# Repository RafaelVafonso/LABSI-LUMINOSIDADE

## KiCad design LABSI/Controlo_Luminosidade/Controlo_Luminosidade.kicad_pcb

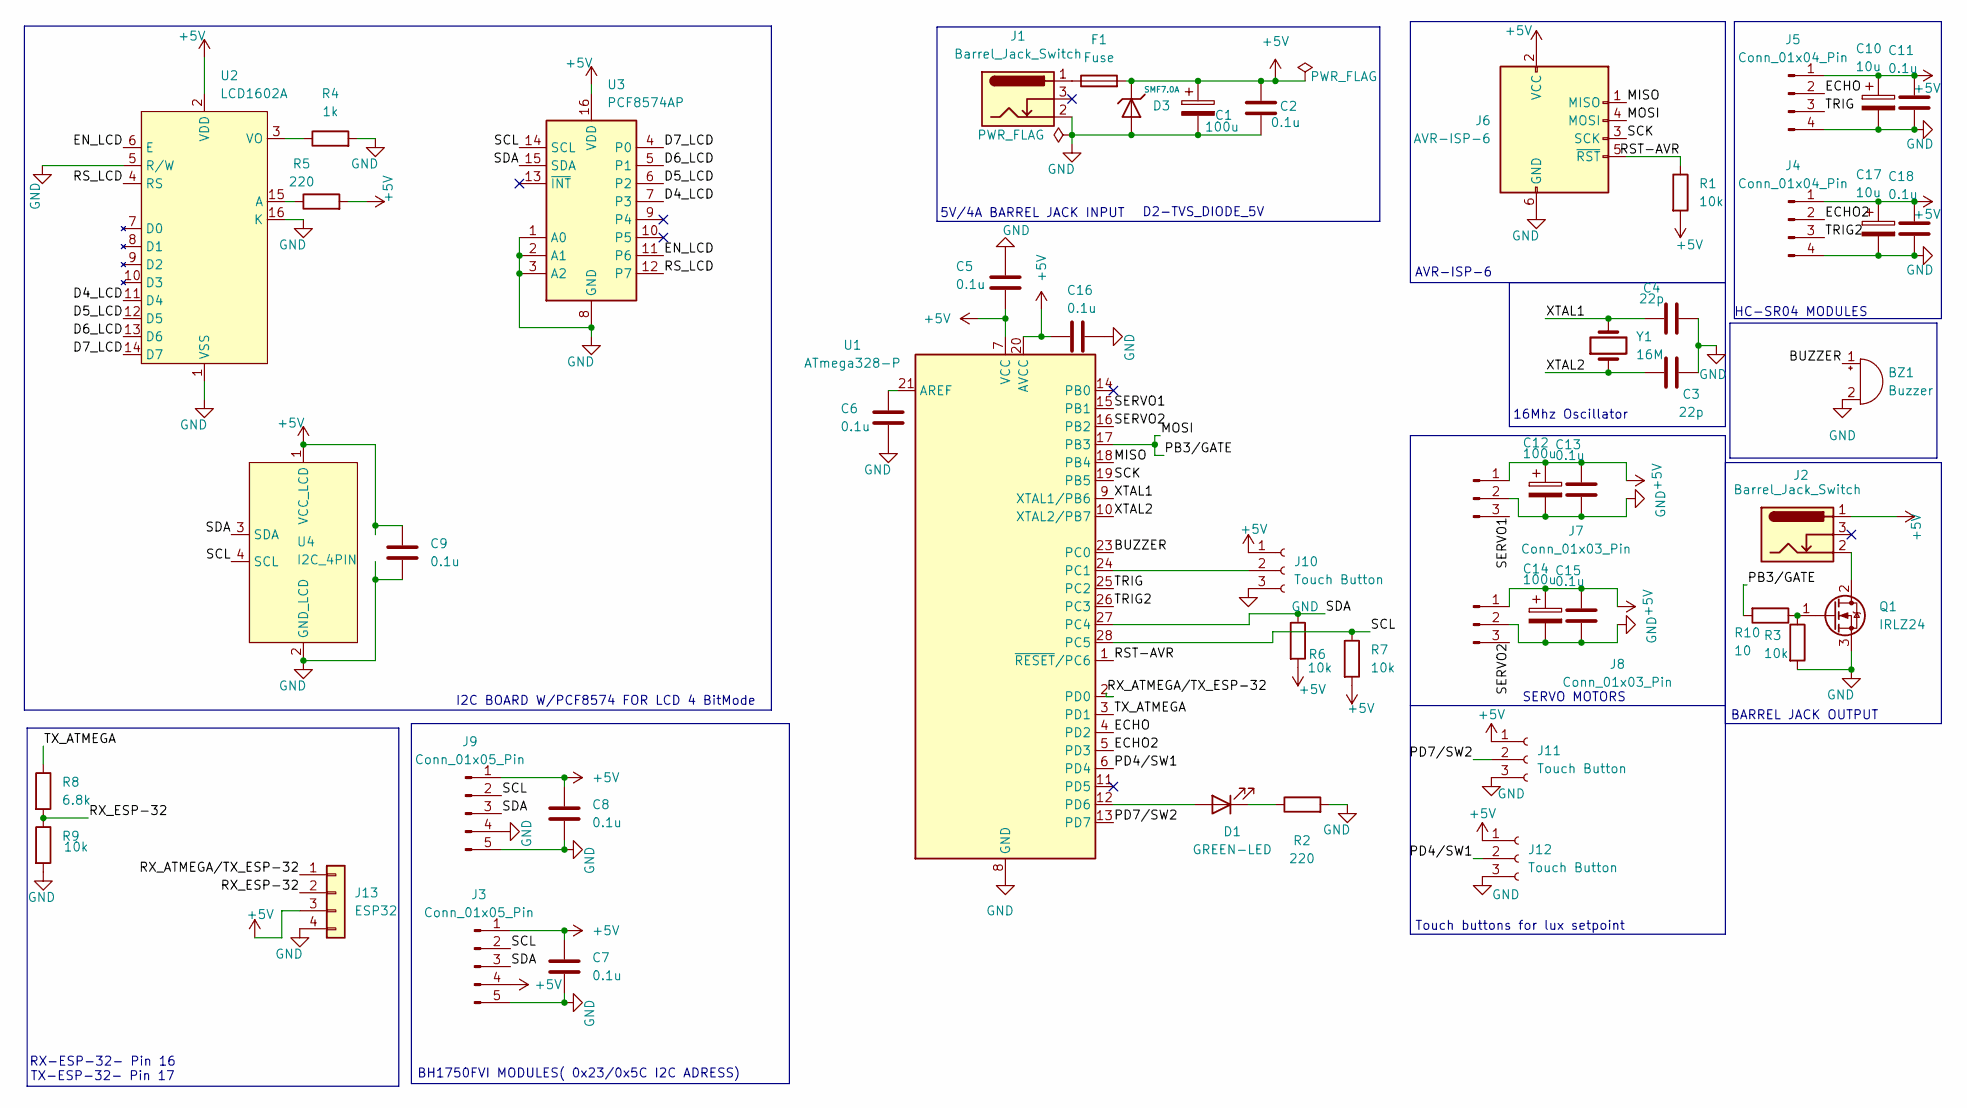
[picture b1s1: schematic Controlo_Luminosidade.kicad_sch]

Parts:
BZ1: Buzzer; Buzzer_12x9.5RM7.6
C1, C12, C14: 100u; C_Radial_D6.3mm_H11.0mm_P2.50mm
C2, C5, C6, C7, C8, C11, C13, C15, C16, C18: 0.1u; C_Disc_D3.0mm_W2.0mm_P2.50mm
C3, C4: 22p; C_Disc_D3.0mm_W2.0mm_P2.50mm
C9: 0.1u
C10, C17: 10u; C_Radial_D6.3mm_H11.0mm_P2.50mm
D1: GREEN-LED; LED_D5.0mm
D3: SMF7.0A; D_SMA; Breakdown Voltage 8.6V; Part SMF7.0A; LCSC C41376088
F1: Fuse; FUSAD2722W65L2250D600
J1, J2: Barrel_Jack_Switch; BarrelJack_Horizontal
J3, J9: Conn_01x05_Pin; PinHeader_1x05_P2.54mm_Vertical
J4, J5: Conn_01x04_Pin; PinSocket_1x04_P2.54mm_Vertical
J6: AVR-ISP-6; PinHeader_2x03_P2.54mm_Vertical
J7, J8: Conn_01x03_Pin; PinHeader_1x03_P2.54mm_Vertical
J10, J11, J12: Touch Button; PinSocket_1x03_P2.54mm_Vertical
J13: ESP32; PinSocket_1x04_P2.54mm_Vertical
Q1: IRLZ24; TO-220-3_Vertical
R1, R3, R6, R7, R9: 10k; R_Axial_DIN0204_L3.6mm_D1.6mm_P5.08mm_Horizontal
R2: 220; R_Axial_DIN0204_L3.6mm_D1.6mm_P5.08mm_Horizontal
R4: 1k
R5: 220
R8: 6.8k; R_Axial_DIN0204_L3.6mm_D1.6mm_P5.08mm_Horizontal
R10: 10; R_Axial_DIN0204_L3.6mm_D1.6mm_P5.08mm_Horizontal
U1: ATmega328-P; DIP-28_W7.62mm
U2: LCD1602A
U3: PCF8574AP
U4: I2C_4PIN; PinSocket_2x02_P2.54mm_Vertical
Y1: 16M; Crystal_HC49-4H_Vertical

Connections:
+5V: C1.1, C2.1, C5.1, C7.1, C8.1, C9.1, C10.1, C11.1, C12.1, C13.1, C14.1, C15.1, C16.1, C17.1, C18.1, D3.1, F1.2, J2.1, J3.1, J3.4, J4.1, J5.1, J6.2 (VCC), J7.1, J8.1, J9.1, J10.1, J11.1, J12.1, J13.3, R1.2, R5.2, R6.2, R7.2, U1.7 (VCC), U1.20 (AVCC), U2.2 (VDD), U3.16 (VDD), U4.1 (VCC_LCD)
/BUZZER: BZ1.1 (+), U1.23 (PC0)
/ECHO: J5.2, U1.4 (PD2)
/ECHO2: J4.2, U1.5 (PD3)
/MISO: J6.1 (MISO), U1.18 (PB4)
/MOSI: J6.4 (MOSI), R10.2, U1.17 (PB3)
/PD4/SW1: J12.2, U1.6 (PD4)
/PD7/SW2: J11.2, U1.13 (PD7)
/RST-AVR: J6.5 (~RST), R1.1, U1.1 (~RESET/PC6)
/RX_ATMEGA/TX_ESP-32: J13.1, U1.2 (PD0)
/RX_ESP-32: J13.2, R8.2, R9.1
/SCK: J6.3 (SCK), U1.19 (PB5)
/SCL: J3.2, J9.2, R7.1, U1.28 (PC5), U3.14 (SCL), U4.4 (SCL)
/SDA: J3.3, J9.3, R6.1, U1.27 (PC4), U3.15 (SDA), U4.3 (SDA)
/SERVO1: J7.3, U1.15 (PB1)
/SERVO2: J8.3, U1.16 (PB2)
/TRIG: J5.3, U1.25 (PC2)
/TRIG2: J4.3, U1.26 (PC3)
/TX_ATMEGA: R8.1, U1.3 (PD1)
/XTAL1: C4.1, U1.9 (XTAL1/PB6), Y1.2
/XTAL2: C3.1, U1.10 (XTAL2/PB7), Y1.1
GND: BZ1.2 (-), C1.2, C2.2, C3.2, C4.2, C5.2, C6.2, C7.2, C8.2, C9.2, C10.2, C11.2, C12.2, C13.2, C14.2, C15.2, C16.2, C17.2, C18.2, D3.2, J1.2, J3.5, J4.4, J5.4, J6.6 (GND), J7.2, J8.2, J9.4, J9.5, J10.3, J11.3, J12.3, J13.4, Q1.3 (S), R2.2, R3.2, R4.2, R9.2, U1.8 (GND), U1.22 (GND), U2.1 (VSS), U2.5 (R/W), U2.16 (K), U3.1 (A0), U3.2 (A1), U3.3 (A2), U3.8 (GND), U4.2 (GND_LCD)
unnamed: D1.2 (A), U1.12 (PD6)
unnamed: D1.1 (K), R2.1
unnamed: F1.1, J1.1
unnamed: J10.2, U1.24 (PC1)
unnamed: J2.2, Q1.2 (D)
unnamed: Q1.1 (G), R3.1, R10.1
unnamed: R4.1, U2.3 (VO)
unnamed: R5.1, U2.15 (A)
unnamed: C6.1, U1.21 (AREF)
unnamed: U2.4 (RS), U3.12 (P7)
unnamed: U2.6 (E), U3.11 (P6)
unnamed: U2.11 (D4), U3.7 (P3)
unnamed: U2.12 (D5), U3.6 (P2)
unnamed: U2.13 (D6), U3.5 (P1)
unnamed: U2.14 (D7), U3.4 (P0)

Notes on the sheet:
D2-TVS_DIODE_5V
RX-ESP-32- Pin 16 TX-ESP-32- Pin 17
I2C BOARD W/PCF8574 FOR LCD 4 BitMode
Touch buttons for lux setpoint
16Mhz Oscillator
5V/4A BARREL JACK INPUT
SERVO MOTORS
BH1750FVI MODULES( 0x23/0x5C I2C ADRESS)
AVR-ISP-6
BARREL JACK OUTPUT
HC-SR04 MODULES

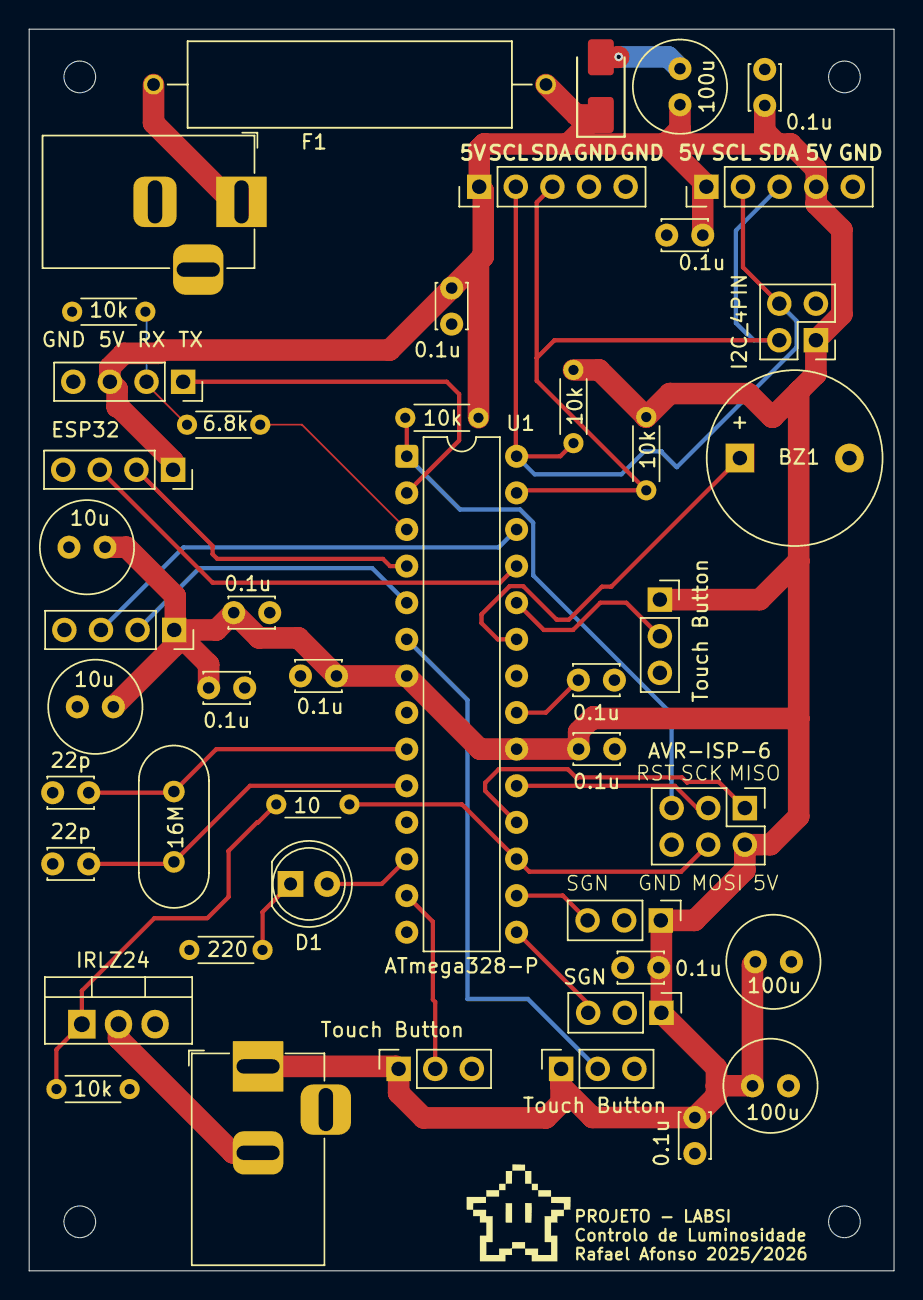
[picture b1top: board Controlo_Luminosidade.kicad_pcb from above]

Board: 2 copper layers, 60.0 x 86.1 mm, 46 parts (0 on the bottom side), 29 nets.

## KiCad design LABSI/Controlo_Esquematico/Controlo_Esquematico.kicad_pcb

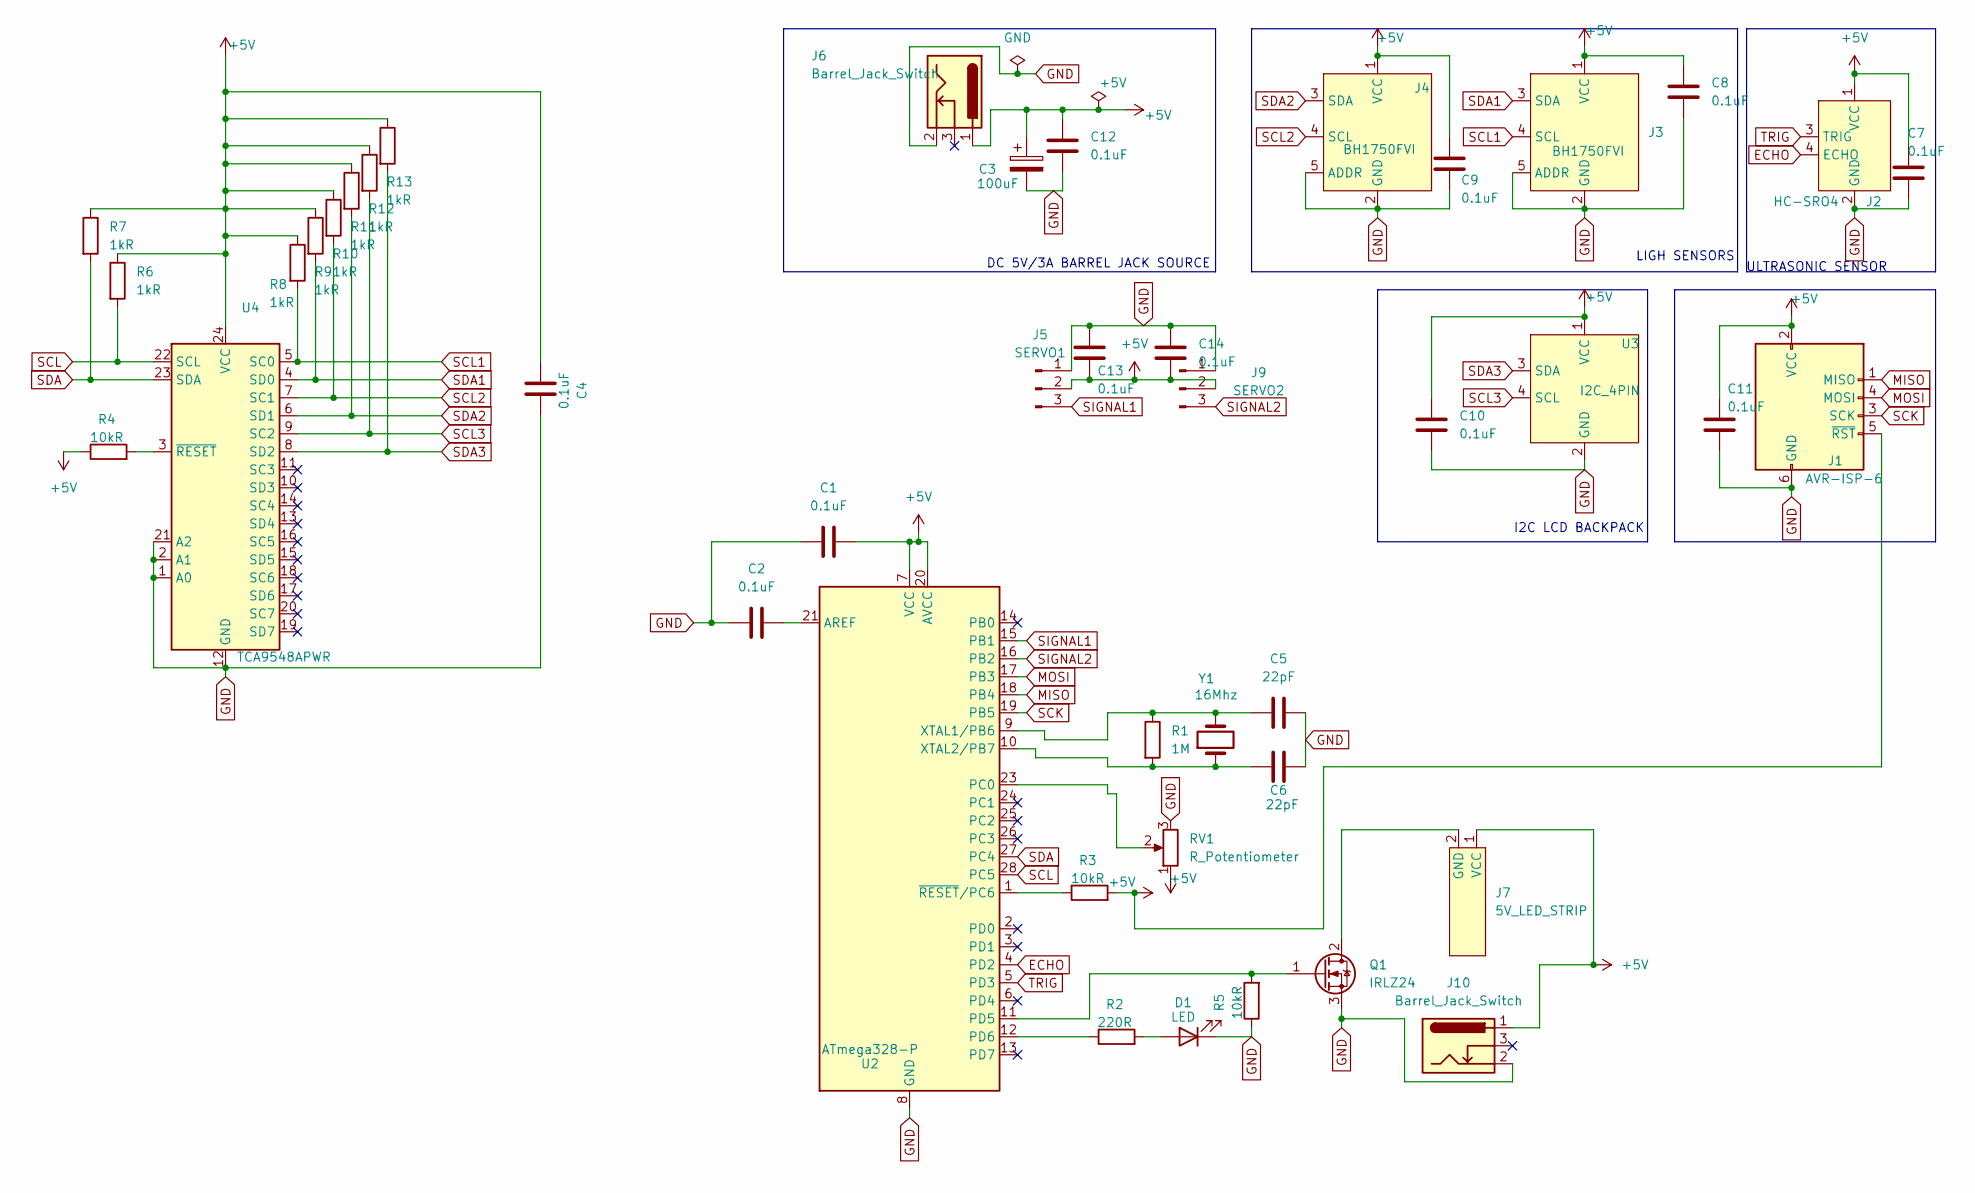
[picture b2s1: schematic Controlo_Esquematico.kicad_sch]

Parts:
C1, C2, C4, C7, C8, C9, C10, C11, C12, C13, C14: 0.1uF; C_Disc_D3.0mm_W2.0mm_P2.50mm
C3: 100uF; CP_Radial_D4.0mm_P1.50mm
C5, C6: 22pF; C_Disc_D3.0mm_W2.0mm_P2.50mm
D1: LED; LED_D5.0mm
J1: AVR-ISP-6; PinHeader_2x03_P2.54mm_Vertical
J2: HC-SRO4; PinHeader_1x04_P2.54mm_Vertical
J3, J4: BH1750FVI; PinHeader_1x05_P2.54mm_Vertical
J5: SERVO1; PinHeader_1x03_P2.54mm_Vertical
J6, J10: Barrel_Jack_Switch; CUI_PJ-067B
J7: 5V_LED_STRIP
J9: SERVO2; PinHeader_1x03_P2.54mm_Vertical
Q1: IRLZ24; TO-220-3_Vertical
R1: 1M; R_Axial_DIN0204_L3.6mm_D1.6mm_P5.08mm_Horizontal
R2: 220R; R_Axial_DIN0204_L3.6mm_D1.6mm_P5.08mm_Horizontal
R3, R4, R5: 10kR; R_Axial_DIN0204_L3.6mm_D1.6mm_P5.08mm_Horizontal
R6, R7, R8, R9, R10, R11, R12, R13: 1kR; R_Axial_DIN0204_L3.6mm_D1.6mm_P5.08mm_Horizontal
RV1: R_Potentiometer; Potentiometer_Alps_RK163_Single_Horizontal
U2: ATmega328-P; DIP-28_W7.62mm
U3: I2C_4PIN; PinHeader_2x02_P2.54mm_Vertical
U4: TCA9548APWR; MODULE_2717
Y1: 16Mhz; Crystal_HC49-4H_Vertical

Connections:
+5V: C1.2, C3.1, C4.1, C7.1, C8.1, C9.1, C10.1, C11.1, C12.1, C13.1, C14.1, J1.2 (VCC), J1.5 (~RST), J2.1 (VCC), J3.1 (VCC), J4.1 (VCC), J5.2, J6.1, J7.1 (VCC), J9.2, J10.1, R3.2, R4.1, R6.1, R7.1, R8.1, R9.1, R10.1, R11.1, R12.1, R13.1, RV1.1, U2.7 (VCC), U2.20 (AVCC), U3.1 (VCC), U4.24 (VCC)
ECHO: J2.4 (ECHO), U2.4 (PD2)
GND: C1.1, C2.1, C3.2, C4.2, C5.2, C6.2, C7.2, C8.2, C9.2, C10.2, C11.2, C12.2, C13.2, C14.2, D1.1 (K), J1.6 (GND), J2.2 (GND), J3.2 (GND), J3.5 (ADDR), J4.2 (GND), J4.5 (ADDR), J5.1, J6.2, J9.1, J10.2, Q1.3 (S), R5.1, RV1.3, U2.8 (GND), U2.22 (GND), U3.2 (GND), U4.1 (A0), U4.2 (A1), U4.12 (GND), U4.21 (A2)
MISO: J1.1 (MISO), U2.18 (PB4)
MOSI: J1.4 (MOSI), U2.17 (PB3)
unnamed: D1.2 (A), R2.2
unnamed: J7.2 (GND), Q1.2 (D)
unnamed: Q1.1 (G), R5.2, U2.11 (PD5)
unnamed: C2.2, U2.21 (AREF)
unnamed: RV1.2, U2.23 (PC0)
unnamed: R2.1, U2.12 (PD6)
unnamed: C5.1, R1.1, U2.9 (XTAL1/PB6), Y1.2
unnamed: C6.1, R1.2, U2.10 (XTAL2/PB7), Y1.1
unnamed: R3.1, U2.1 (~RESET/PC6)
unnamed: R4.2, U4.3 (~RESET)
SCK: J1.3 (SCK), U2.19 (PB5)
SCL: R6.2, U2.28 (PC5), U4.22 (SCL)
SCL1: J3.4 (SCL), R8.2, U4.5 (SC0)
SCL2: J4.4 (SCL), R10.2, U4.7 (SC1)
SCL3: R12.2, U3.4 (SCL), U4.9 (SC2)
SDA: R7.2, U2.27 (PC4), U4.23 (SDA)
SDA1: J3.3 (SDA), R9.2, U4.4 (SD0)
SDA2: J4.3 (SDA), R11.2, U4.6 (SD1)
SDA3: R13.2, U3.3 (SDA), U4.8 (SD2)
SIGNAL1: J5.3, U2.15 (PB1)
SIGNAL2: J9.3, U2.16 (PB2)
TRIG: J2.3 (TRIG), U2.5 (PD3)

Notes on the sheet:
LIGH SENSORS
ULTRASONIC SENSOR
I2C LCD BACKPACK
DC 5V/3A BARREL JACK SOURCE

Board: 2 copper layers, 42 parts (0 on the bottom side), 26 nets, no tracks yet.

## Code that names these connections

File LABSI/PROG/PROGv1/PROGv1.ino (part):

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
#define MODE_AUTOMATIC 0
#define MODE_MANUAL 1
#define BOTAO_TOUCH PC1
#define BOTAO_MAIS PD4 // Botão Aumentar
#define BOTAO_MENOS PD7 // Botão Diminuir
#define BUZZER_PIN PC0 // Buzzer (PC0)

// --- CONFIGURAÇÃO UART (ESP32) ---
#define BAUD 9600
#define UBRR_VAL ((F_CPU/16/BAUD)-1)

#define SONAR1_TRIG PC2
#define SONAR1_ECHO PD2
#define SONAR2_TRIG PC3
#define SONAR2_ECHO PD3
// 20 cm ~ 1156 us de echo -> com Timer1 a 4 us/tick => ~290 ticks
#define SONAR_THRESHOLD_TICKS_20CM 290
#define LUX_STEP 50
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#define EEP_POS1_ADDR (uint16_t*)0x00
#define EEP_POS2_ADDR (uint16_t*)0x02

#define GATE_PIN PB3
#define MAX_LED_PWM 255
// --- VARIÁVEIS DE CONTROLO DE TEMPO E ESTADO ---
volatile uint16_t g_delay_counter_2ms = 0; // Contador principal, decrementa a cada 2ms
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	// Controlo do Buzzer
	if(g_buzzer_counter > 0) {
		g_buzzer_counter--;
		// Alterna o Buzzer (PC0) a cada 50ms (25 ticks)
		if(g_buzzer_counter % 25 == 0) {
			PORTC ^= (1 << BUZZER_PIN);
		}
	} else {
		PORTC &= ~(1 << BUZZER_PIN); // Desliga o Buzzer
	}
	g_contador++;
	if(g_contador >= 250) {
		PORTD ^= (1 << PD6);
		g_contador = 0;
	}
	g_display_counter++;

}
ISR(PCINT1_vect) {
	uint8_t current_state = PINC & (1 << PC1);
	if(current_state > g_prev_pc1_state) {
		// Transição de 0 para 1 detectada
		if(!g_mode_locked) {
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	TWCR |= (1 << TWEN);
	TWSR = 0;
	TWBR = 12;
	DDRC &= ~((1 << PC4) | (1 << PC5));
	PORTC |= (1 << PC4) | (1 << PC5);
}
void i2c_start(void) {
	TWCR = (1 << TWINT) | (1 << TWSTA) | (1 << TWEN);
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}
// --- Timer 0 for 2ms interrupt ---
void onda1Hz_init(void) {
	DDRD |= (1 << PD6);
	PORTD &= ~(1 << PD6);
	TCCR0A = (1 << WGM01); // CTC Mode
	TCCR0B = (1 << CS02) | (1 << CS00); // Prescaler 1024
	OCR0A = 31; // (16M / 1024) / (31+1) = 500 Hz (2ms)
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	OCR2A = 0;
}
void pwm_Servo_init(void) {
	DDRB |= (1 << PB1) | (1 << PB2);
	TCCR1A |= (1 << COM1A1) | (1 << COM1B1)| (1 << WGM11);//PC
	TCCR1B |= (1 << WGM13) | (1 << CS11) | (1 << CS10) | (1 << ICNC1); // prescaler 64, noise cancelling
	ICR1 = 2500; // 20 ms (50 Hz)
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	OCR1B = 188;
}
void buttons_inic(void) {
	// Botão touch PC1
	DDRC &= ~(1 << BOTAO_TOUCH);
	PORTC &= ~(1 << BOTAO_TOUCH);
	// Botões +/- em PD4 e PD7
	DDRD &= ~((1 << BOTAO_MAIS) | (1 << BOTAO_MENOS));
	PORTD &= ~((1 << BOTAO_MAIS) | (1 << BOTAO_MENOS));
	// BUZZER
	DDRC |= (1 << BUZZER_PIN);
	PORTC &= ~(1 << BUZZER_PIN);
	// Sonares: TRIG como saída, ECHO como entrada
	DDRC |= (1 << SONAR1_TRIG) | (1 << SONAR2_TRIG);
	DDRD &= ~((1 << SONAR1_ECHO) | (1 << SONAR2_ECHO));
	PORTD &= ~((1 << SONAR1_ECHO) | (1 << SONAR2_ECHO)); // sem pull-up
	// Interrupção de PC1 (botão touch)
	PCICR |= (1 << PCIE1);
	PCMSK1 |= (1 << PCINT9);
}
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  static uint8_t stable_state_1 = 0;
  static uint8_t stable_state_2 = 0;

  uint8_t trig_pin, echo_pin;
  uint32_t *last_time;
  uint8_t *stable_state;

  // Seleciona sonar
  if (sonar_id == 1) {
      trig_pin = SONAR1_TRIG;
      echo_pin = SONAR1_ECHO;
      last_time = &last_trigger_time_1;
      stable_state = &stable_state_1;
  } else {
      trig_pin = SONAR2_TRIG;
      echo_pin = SONAR2_ECHO;
      last_time = &last_trigger_time_2;
      stable_state = &stable_state_2;
  }
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  for (uint8_t i = 0; i < 3; i++)
  {
      // Trigger de 10 us
      PORTC &= ~(1 << trig_pin);
      delay_us(2);
      PORTC |= (1 << trig_pin);
      delay_us(10);
      PORTC &= ~(1 << trig_pin);

      delay_us(200); // evita eco imediato

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      uint16_t timeout = 0;

      // Espera echo subir
      while (!(PIND & (1 << echo_pin)) && timeout < 7500) timeout++;
      if (timeout >= 7500) { sei(); continue; }

      uint16_t start = TCNT1;
      timeout = 0;

      // Espera echo descer
      while ((PIND & (1 << echo_pin)) && timeout < 30000) timeout++;
      uint16_t end = TCNT1;

      sei();
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
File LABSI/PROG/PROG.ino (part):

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#define F_CPU 16000000UL    

// LCD PIN MAPPINGS (4-bit mode)
#define LCD_RS PORTD |= (1 << PD7)  // RS Pin 7
#define LCD_RS_LOW PORTD &= ~(1 << PD7)

#define LCD_EN PORTB |= (1 << PB0)  // EN Pin 8
#define LCD_EN_LOW PORTB &= ~(1 << PB0)

#define LCD_D4 PORTD |= (1 << PD0)  // D4 Pin 0
#define LCD_D4_LOW PORTD &= ~(1 << PD0)

#define LCD_D5 PORTD |= (1 << PD1)  // D5 Pin 1
#define LCD_D5_LOW PORTD &= ~(1 << PD1)

#define LCD_D6 PORTD |= (1 << PD4)  // D6 Pin 4
#define LCD_D6_LOW PORTD &= ~(1 << PD4)

#define LCD_D7 PORTD |= (1 << PD5)  // D7 Pin 5
#define LCD_D7_LOW PORTD &= ~(1 << PD5)


#define BH1750_ADDR1 0x23  //Default I2C address (0x23) ADDR GND
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    flag_2ms = 1;
    contador++;
    if (contador >= 250) { // 250 * 2ms = 0.5s
        PORTD ^= (1 << PD6); // Toggle PD6 for 1Hz signal check
        contador = 0;   
    }
    display_counter++;
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void lcd_init(void) {
    // Setup LCD control and data pins as outputs
    DDRB |= (1 << PB0);  // EN output
    DDRD |= (1 << PD0) | (1 << PD1) | (1 << PD4) | (1 << PD5) | (1 << PD7);  // D4-D7 and RS outputs
    
    delay_ms(50);  // Power-on wait
    
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    TWCR |= (1<< TWEN); //twi controla os pinos scl e sda
    TWSR = 0;// prescaler a 1
    TWBR =17;// SCL a 320khz
    DDRC &= ~((1 << PC4) | (1 << PC5)); 
    PORTC |= (1 << PC4) | (1 << PC5);
}

void i2c_start(void){
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}
void pwm_Servo_init(void){

DDRB |= (1 << PB1);
TCCR1A |= (1 << COM1A1) | (1 << WGM11);
TCCR1B |= (1 << WGM13) | (1 << CS11) | (1 << CS10);
ICR1 = 2500;
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}


// --- Timer 0 for 2ms interrupt (for timing and toggling PD6) ---
void onda1Hz_init(void) {
    DDRD |= (1 << PD6); // PD6 as output (LED check)
    PORTD &= ~(1 << PD6); // Initial state low

    // Timer0 CTC mode (Clear Timer on Compare Match)
    TCCR0A = (1 << WGM01);   // CTC mode
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
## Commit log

2025-11-12 added lcd through i2c, code for timer1(servo)
2025-11-18 micro standalone, bug it reading lux sensors
2025-11-19 rotina maquina de estados inic; i2c, 2 sensors bug fixed, button logic added
2025-11-20 maquina estados controlo adc, butao para modos, mapeamento para saltos de 50 e fixação setpoint
2025-11-24 botoes para setpoint, buzzer adicionado, motor adicionado
2025-11-26 botoes touch sem debounce a funcionar, logica motor a funcionar
2025-11-26 botoes touch com debounce, logica do motor a funcionar
2025-11-27 inicio sensor de gesto
2025-11-27 sensor de gesto calibraçao
2025-12-03 sonar not working, integration with esp32 iot,
2025-12-04 uart init and uart check cmds, not working atmega side
2025-12-06 controlo web funcional. falta adicionar controlo da fita led entre mudanças de estado; adicionar oc1b com o segundo motor; limitar duty cycle da fita a 80%; criar botao web para desligar fita; adicio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
2025-12-09 pcb finalizado, gee«rbers gerados, falta desenvolver o que falta no ultimo commit
2025-12-10 pcb mudado, adicionada fusivel de 5A e Diodo tvs na entrada como proteção, gerbers gerados nao foi mexido no firmware
2025-12-23 pcb impresso. falta desenvolver codigo temporizaçao para os motores, trocar codigo display para oled i2c
2026-01-09 motores com posiçao virtual, desenvolver sistema para acertar posiçoes. sonares nao estao a fucnionar
2026-01-10 afinar posiçao virtual. sonares estao a fucnionar
2026-01-11 ajustar pos. relatorio entregue
